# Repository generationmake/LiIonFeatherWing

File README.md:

# LiIonFeatherWing
Feather Wing with a 18650 LiIon-battery and various mounting options compatible with Adafruit feather

## PCB

### Top

### Bottom

## Mounting Options

### BikeAdapter

The BikeAdapter needs to be 3D printed and screwed to the LiIonFeatherWing PCB with two M3 screws and nuts. It can be attached to the handlebar using an o-ring.

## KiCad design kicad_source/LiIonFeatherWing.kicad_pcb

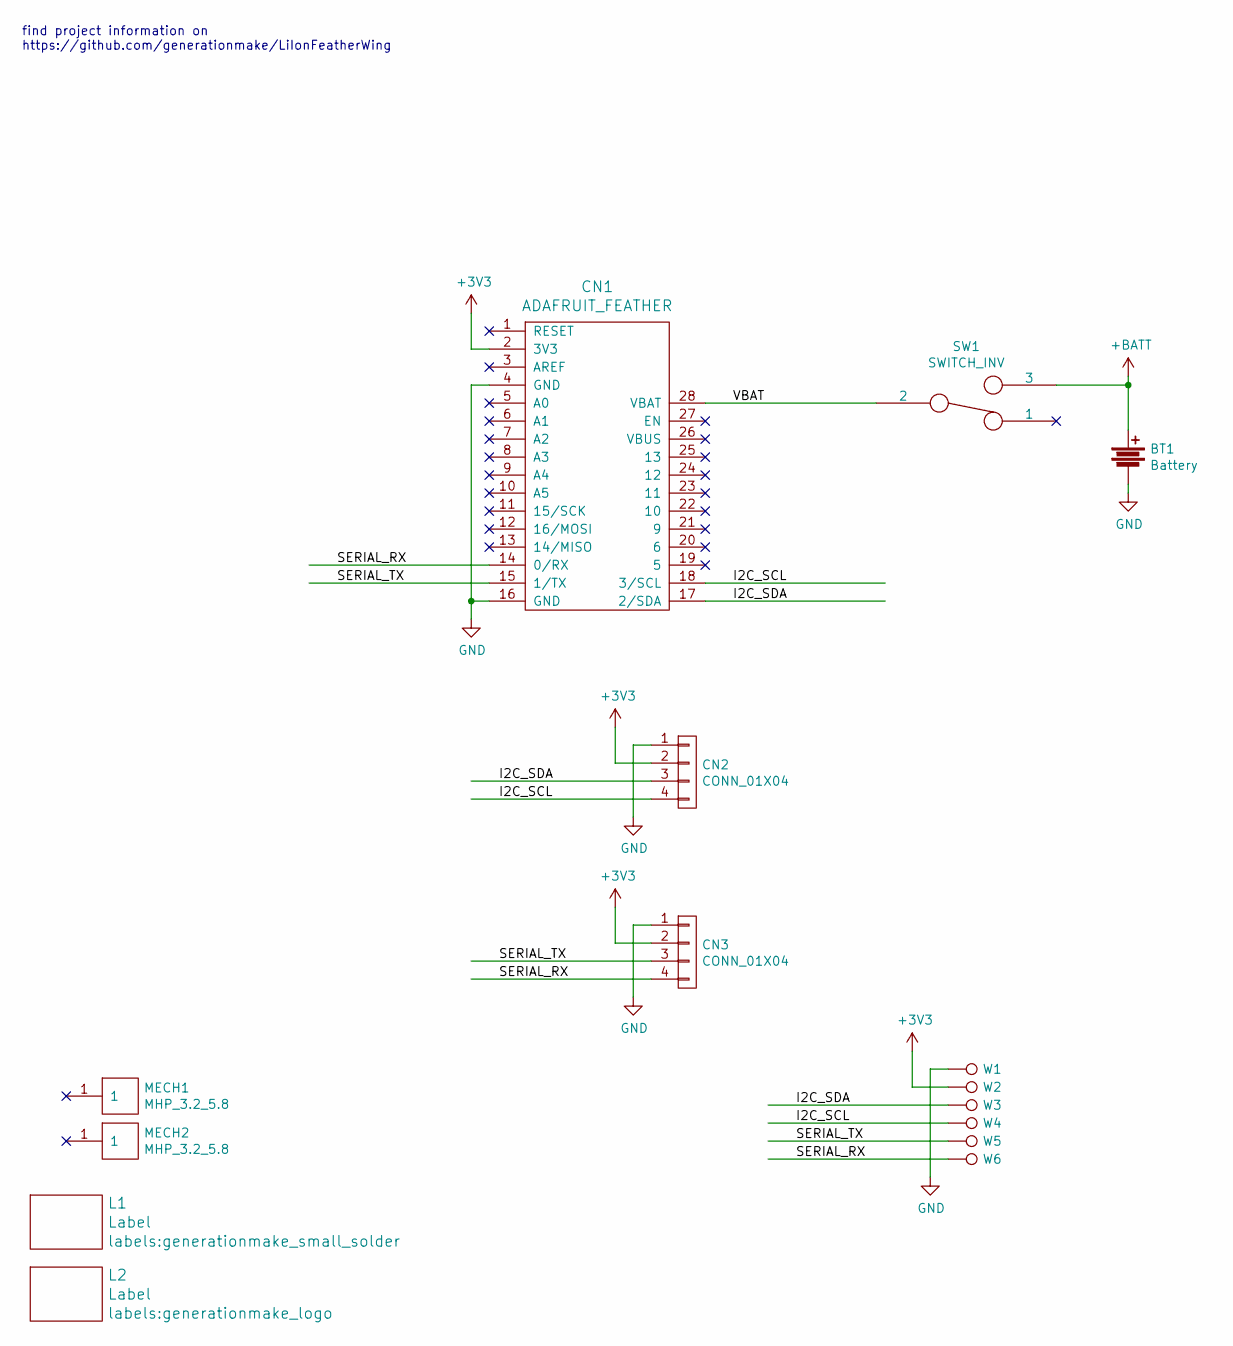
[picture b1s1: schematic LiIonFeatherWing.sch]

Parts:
BT1: Battery; KEYSTONE_1043
CN1: ADAFRUIT_FEATHER; ADAFRUIT_FEATHER_HOLES
CN2, CN3: CONN_01X04; Connectors_JST_SM04B-SRSS-TB
L1: Label; generationmake_small_solder
L2: Label; generationmake_logo
MECH1, MECH2: MHP_3.2_5.8
SW1: SWITCH_INV; WE_450404015514
W1, W2, W3, W4, W5, W6: TEST_1P; SolderWirePad_single_0-8mmDrill

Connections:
+3V3: CN1.2 (3V3), CN2.2, CN3.2, W2.1
+BATT: BT1.1, SW1.3
/I2C_SCL: CN1.18 (3/SCL), CN2.4, W4.1
/I2C_SDA: CN1.17 (2/SDA), CN2.3, W3.1
/SERIAL_RX: CN1.14 (0/RX), CN3.4, W6.1
/SERIAL_TX: CN1.15 (1/TX), CN3.3, W5.1
/VBAT: CN1.28 (VBAT), SW1.2
GND: BT1.2, CN1.4 (GND), CN1.16 (GND), CN2.1, CN3.1, W1.1

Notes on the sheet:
find project information on https://github.com/generationmake/LiIonFeatherWing

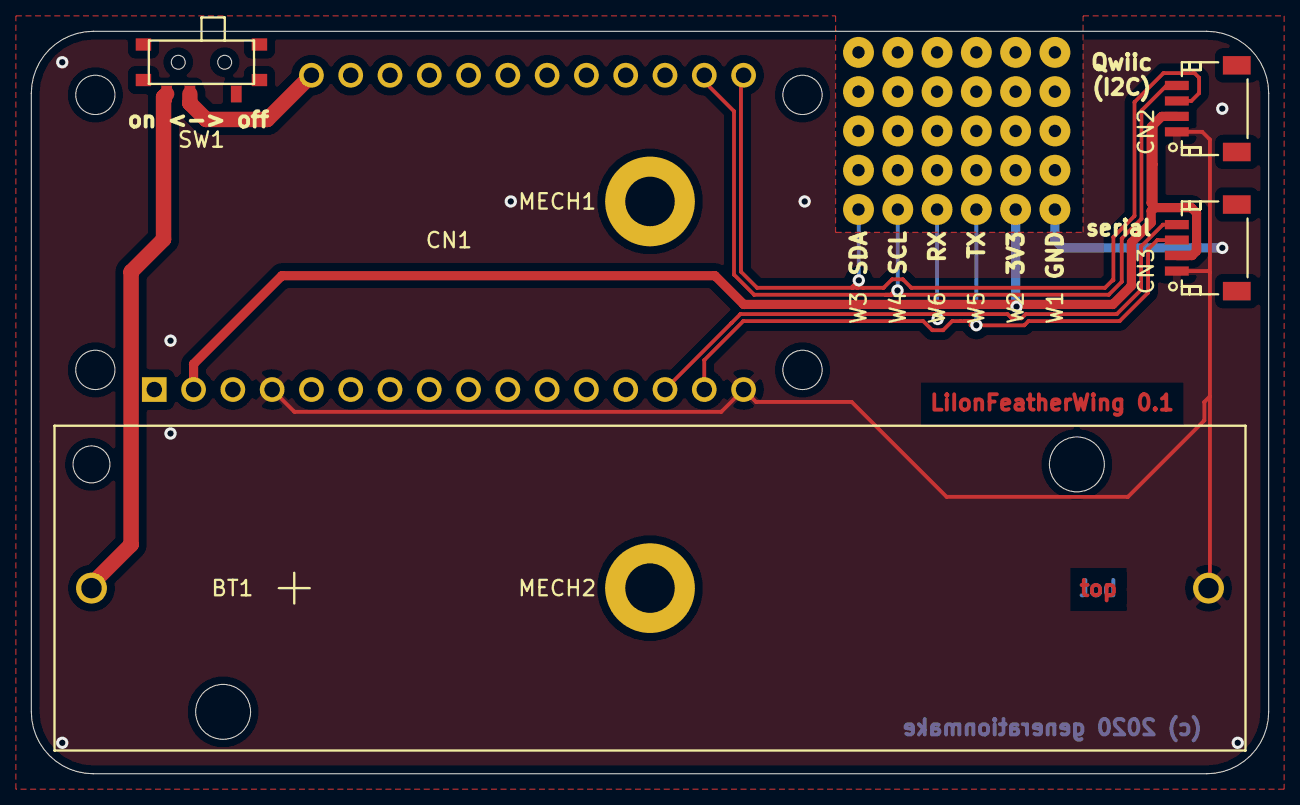
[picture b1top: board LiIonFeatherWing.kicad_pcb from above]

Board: 2 copper layers, 80.0 x 48.0 mm, 15 parts (1 on the bottom side), 8 nets.

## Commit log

2020-10-14 added FreeCAD file for BikeAdapter
2020-10-14 added stl file for BikeAdapter
2020-10-14 added kicad project
2020-10-15 added mounting holes and labels
2020-10-15 added testpoints and array
2020-10-15 added schematic pdf, added images, updated project information
2020-10-15 added step model of PCB, updated BikeAdapter to fit to THT parts on PCB, generated rendering with BikeAdapter
2020-11-06 updated bike adapter for fastening with cable tie
2020-11-06 renamed existing bike adapter and made new adapter for 22.2 mm handle bar
2020-11-06 added new bike adapter with hole for cable tie
2020-11-06 updated stl file
2020-11-07 increased standoff height for bike adapter with cable tie by 8 mm

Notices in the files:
kicad_source/LiIonFeatherWing.kicad_pcb:
(c) 2020 generationmake
